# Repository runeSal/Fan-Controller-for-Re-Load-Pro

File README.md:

Fan-Controller-for-Re-Load-Pro
==============================

DIY Fan Controller for Re:Load Pro

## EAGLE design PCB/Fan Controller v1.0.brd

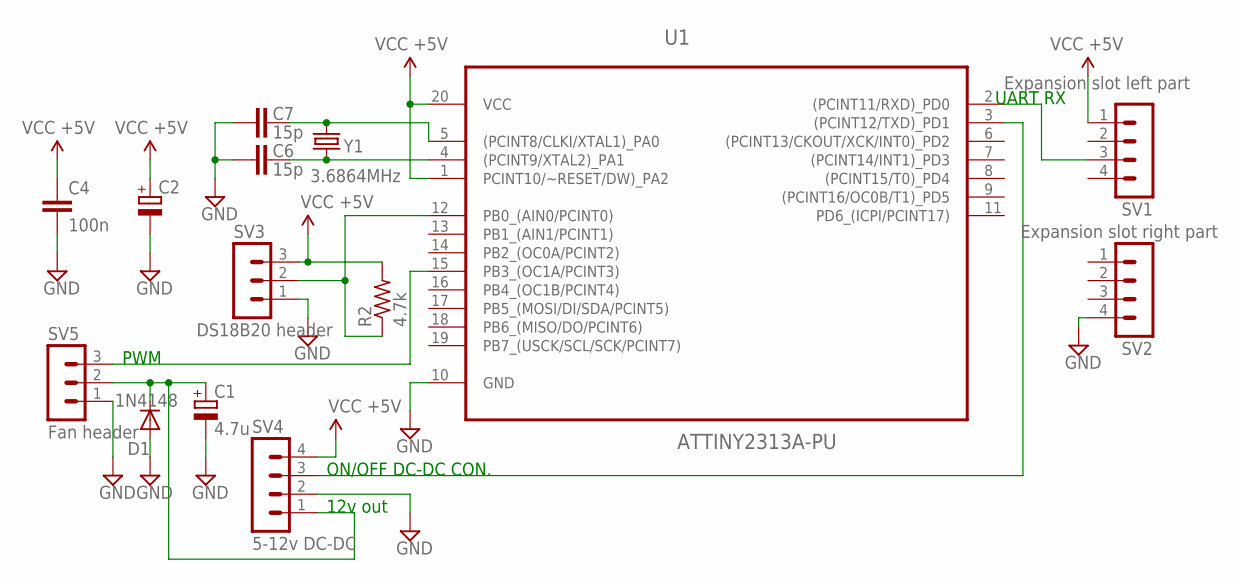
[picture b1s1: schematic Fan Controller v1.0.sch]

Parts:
C1: 4.7u; E2,5-6E
C2: CPOL-EUE5-6; E5-6
C4: 100n; C0805K
C6, C7: 15p; C0805K
D1: 1N4148; DO35-7
R2: 4.7k; R1206
SV1: Expansion slot left part; MA04-1
SV2: Expansion slot right part; MA04-1
SV3: DS18B20 header; MA03-1
SV4: 5-12v DC-DC; MA04-1
SV5: Fan header; MA03-1
U1: ATTINY2313A-PU; DIP254P762X533-20
Y1: 3.6864MHz; HC49U-V

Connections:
12VOUT: C1.+, D1.C, SV4.1, SV5.2
GND: C1.-, C2.-, C4.2, C6.2, C7.2, D1.A, SV2.4, SV3.1, SV4.2, SV5.1, U1.10 (GND)
unnamed: SV1.3, U1.2 ((PCINT11/RXD)_PD0)
unnamed: C7.1, U1.5 ((PCINT8/CLKI/XTAL1)_PA0), Y1.2
unnamed: SV5.3, U1.15 (PB3_(OC1A/PCINT3))
unnamed: C6.1, U1.4 ((PCINT9/XTAL2)_PA1), Y1.1
unnamed: R2.1, SV3.2, U1.12 (PB0_(AIN0/PCINT0))
unnamed: SV4.3, U1.3 ((PCINT12/TXD)_PD1)
VCC: C2.+, C4.1, R2.2, SV1.1, SV3.3, SV4.4, U1.1 (PCINT10/~RESET/DW)_PA2), U1.20 (VCC)

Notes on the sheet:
ON/OFF DC-DC CON.
12v out
PWM
UART RX

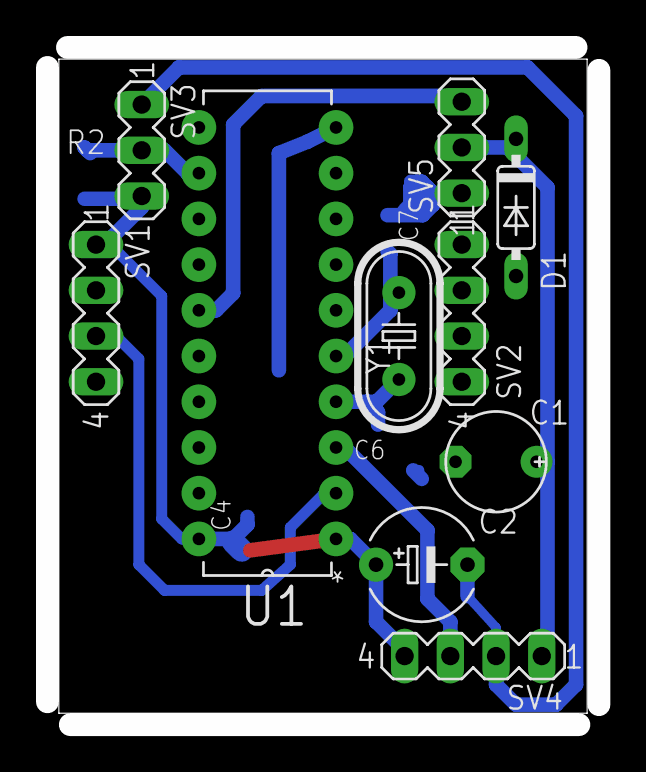
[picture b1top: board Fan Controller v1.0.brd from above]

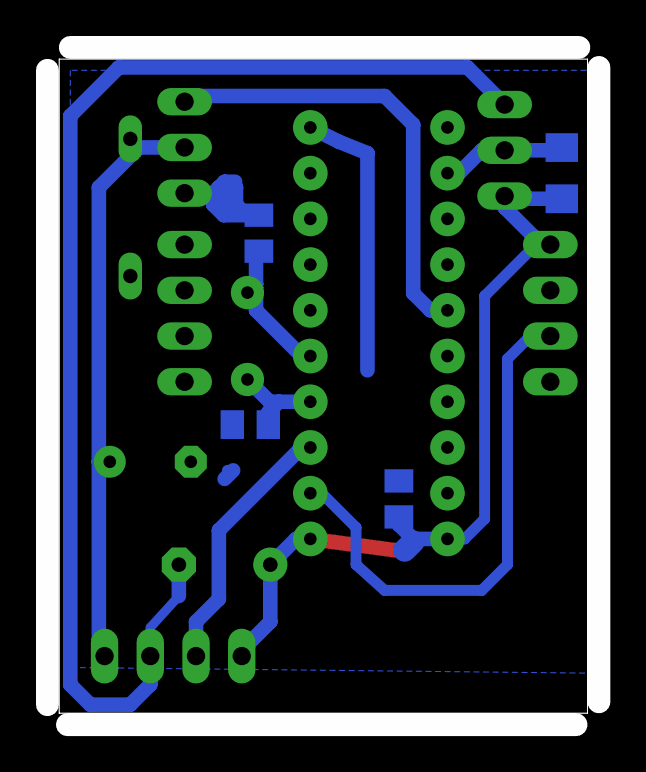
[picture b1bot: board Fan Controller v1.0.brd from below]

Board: 2 copper layers, 30.6 x 37.6 mm, 14 parts (4 on the bottom side), 9 nets.

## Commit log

2014-11-20 Revert "Create LICENSE.md"
    This reverts commit 6a447f4b575f4aa4686efe68836bd72db6dcb81c.
2014-11-20 Eagle project v1.0
2014-11-20 Source code
2014-11-20 Programming files
2014-11-20 fuse support
2014-11-21 schematic uploaded
2014-11-21 name update

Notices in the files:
parts and their libraries:
SparkFun-Aesthetics: Licensing: Creative Commons ShareAlike 4.0 International - https://creativecommons.org/licenses/by-sa/4.0
